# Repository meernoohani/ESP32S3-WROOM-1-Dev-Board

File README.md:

# ESP32-S3-N16R8 Custom Dev Board

A compact, high-performance development board powered by the **ESP32-S3-WROOM-1-N16R8** module, designed in **KiCad 9.0**. This design focuses on maximizing I/O accessibility and providing dual USB-C functionality for both debugging and native USB applications.

## 🛠 Features
* **MCU:** ESP32-S3 (Dual-core @ 240MHz)
* **Memory:** 16MB Flash / 8MB Octal PSRAM (N16R8 variant)
* **Connectivity:**
    * **USB-C (UART):** Dedicated interface for programming and debugging.
    * **USB-C (Native):** Direct access to S3 USB OTG pins.
* **I/O:** Full breakout of all usable GPIOs to 0.1" (2.54mm) headers.
* **Design Tool:** KiCad 9.0

## ⚙️ Hardware Setup
To utilize the 16MB Flash and 8MB PSRAM in your IDE (Arduino/ESP-IDF), use the following settings:

| Setting | Value |
| :--- | :--- |
| **Board** | ESP32S3 Dev Module |
| **Flash Mode** | QIO |
| **Flash Size** | 16MB |
| **PSRAM** | OPI PSRAM |

## 📦 Production Files
This repository includes production-ready files optimized for manufacturing via **JLCPCB**, located in the `/JLCPCB BOM & Gerber Files` folder. This includes:
* Gerber Files
* Drill Files
* BOM (Bill of Materials)
* CPL (Component Placement List / Pick-and-Place)

---
*Note: This project is shared for reference and educational purposes.*

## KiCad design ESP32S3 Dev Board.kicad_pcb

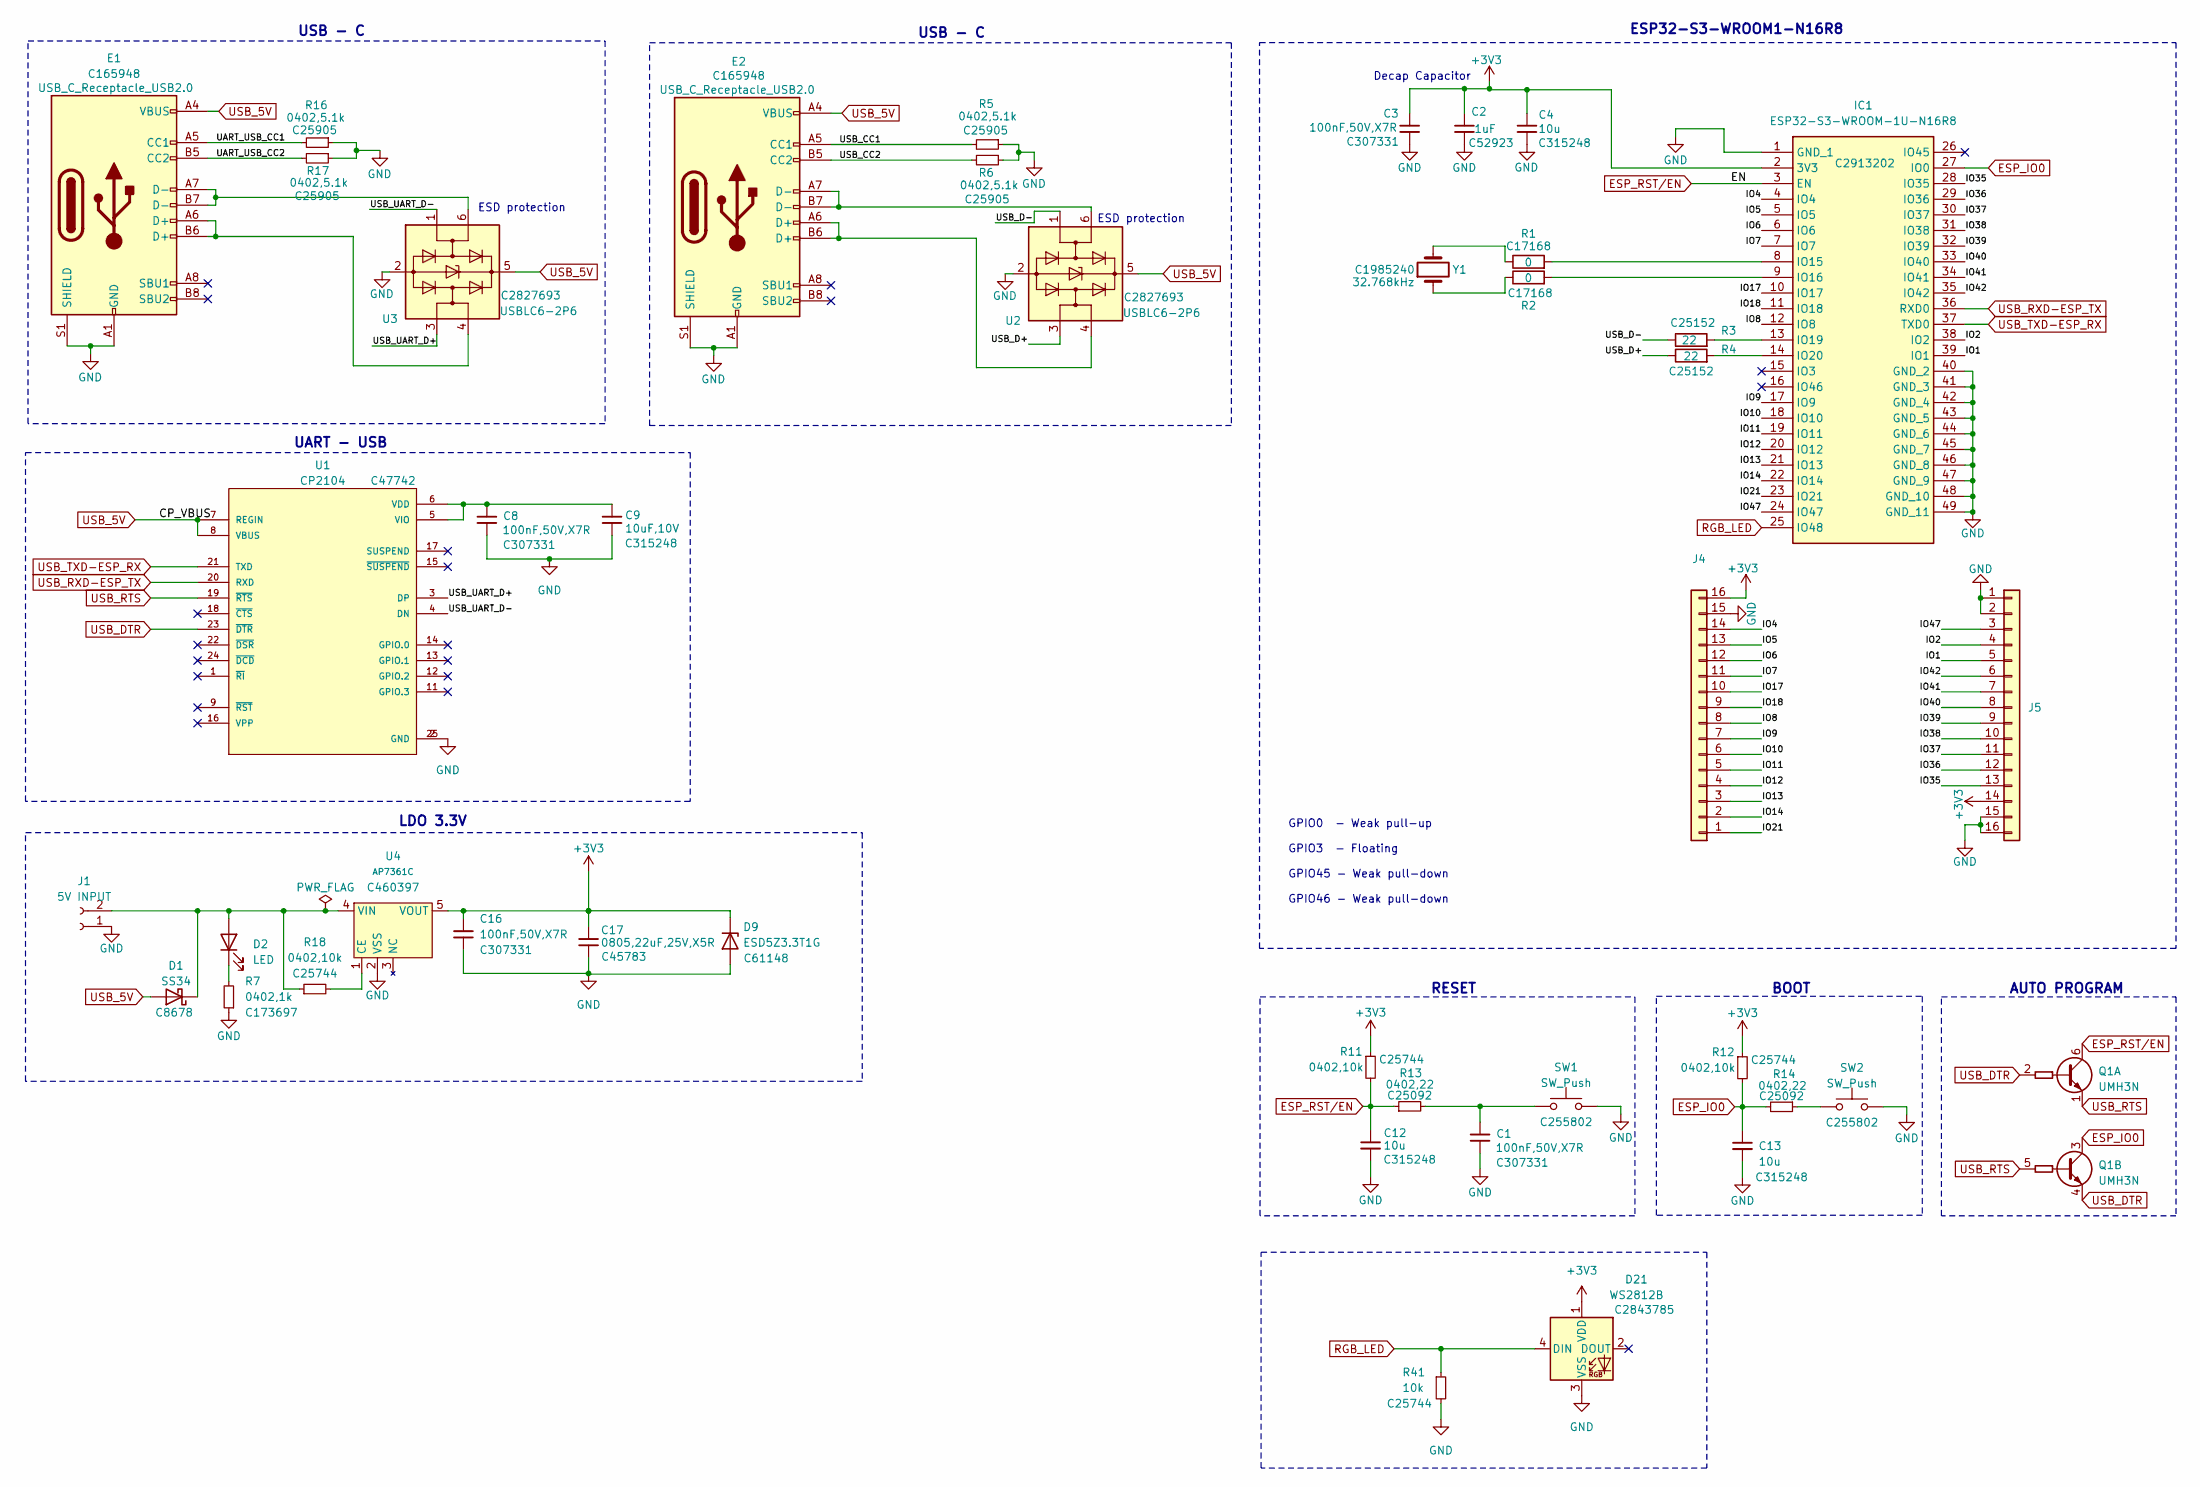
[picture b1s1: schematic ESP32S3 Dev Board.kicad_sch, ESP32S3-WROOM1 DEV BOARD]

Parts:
C1, C3, C8, C16: 100nF,50V,X7R; C_0402_1005Metric; MFGPN CL05B104KB54PNC; LCSC C307331
C2: 1uF; C_0402_1005Metric; MFGPN CL05A105KA5NQNC; LCSC C52923
C4: 10u; C_0402_1005Metric; MFGPN CL05B104KB54PNC; LCSC C315248
C9: 10uF,10V; C_0402_1005Metric; MFGPN CL05B104KB54PNC; LCSC C315248
C12, C13: 10u; C_0402_1005Metric; LCSC C315248
C17: 0805,22uF,25V,X5R; C_0805_2012Metric; MFGPN CL21A226MAQNNNE; LCSC C45783
D1: SS34; D_SMA; LCSC C8678
D2: LED; LED_0603_1608Metric
D9: ESD5Z3.3T1G; D_SOD-523; LCSC C61148
D21: WS2812B; LED_WS2812B_PLCC4_5.0x5.0mm_P3.2mm; LCSC C2843785
E1, E2: USB_C_Receptacle_USB2.0; USB_C; LCSC C165948
IC1: ESP32-S3-WROOM-1U-N16R8; ESP32S3WROOM1UN16R8; Mouser Part Number 356-ESP32S3WM1UN16R8
J1: 5V INPUT; PinHeader_1x02_P2.54mm_Vertical
J4, J5: Conn_01x16; PinHeader_1x16_P2.54mm_Vertical
Q1: UMH3N; SOT-363_SC-70-6; LCSC C62892
R1, R2: 0; C_0402_1005Metric; LCSC C17168
R3, R4: 22; C_0402_1005Metric; LCSC C25152
R5, R6, R16, R17: 0402,5.1k; R_0402_1005Metric; MFGPN 0402WGF5101TCE; LCSC C25905
R7: 0402,1k; R_0402_1005Metric; MFGPN 0402WGF1002TCE; LCSC C173697
R11, R12, R18: 0402,10k; R_0402_1005Metric; MFGPN 0402WGF1002TCE; LCSC C25744
R13, R14: 0402,22; R_0402_1005Metric; MFGPN 0402WGF220JTCE; LCSC C25092
R41: 10k; R_0402_1005Metric; LCSC C25744
SW1, SW2: SW_Push; SW_SPST_CK_RS282G05A3; LCSC C255802
U1: CP2104; CP2104_QFN50P400X400X80-25N; PARTREV 1.0; LCSC C47742
U2, U3: USBLC6-2P6; SOT-666; LCSC C2827693
U4: AP7361C; SOT-89-5; LCSC C460397
Y1: 32.768kHz; Crystal_SMD_3215-2Pin_3.2x1.5mm; LCSC C1985240

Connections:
+3V3: C2.1, C3.1, C4.1, C16.1, C17.1, D9.1 (K), D21.1 (VDD), IC1.2 (3V3), J4.16, J5.14, R11.1, R12.1, U4.5 (VOUT)
/IO1: IC1.39 (IO1), J5.5
/IO2: IC1.38 (IO2), J5.4
/IO4: IC1.4 (IO4), J4.14
/IO5: IC1.5 (IO5), J4.13
/IO6: IC1.6 (IO6), J4.12
/IO7: IC1.7 (IO7), J4.11
/IO8: IC1.12 (IO8), J4.8
/IO9: IC1.17 (IO9), J4.7
/IO10: IC1.18 (IO10), J4.6
/IO11: IC1.19 (IO11), J4.5
/IO12: IC1.20 (IO12), J4.4
/IO13: IC1.21 (IO13), J4.3
/IO14: IC1.22 (IO14), J4.2
/IO17: IC1.10 (IO17), J4.10
/IO18: IC1.11 (IO18), J4.9
/IO21: IC1.23 (IO21), J4.1
/IO35: IC1.28 (IO35), J5.13
/IO36: IC1.29 (IO36), J5.12
/IO37: IC1.30 (IO37), J5.11
/IO38: IC1.31 (IO38), J5.10
/IO39: IC1.32 (IO39), J5.9
/IO40: IC1.33 (IO40), J5.8
/IO41: IC1.34 (IO41), J5.7
/IO42: IC1.35 (IO42), J5.6
/IO47: IC1.24 (IO47), J5.3
/UART_USB_CC1: E1.A5 (CC1), R16.2
/UART_USB_CC2: E1.B5 (CC2), R17.2
/USB_CC1: E2.A5 (CC1), R5.2
/USB_CC2: E2.B5 (CC2), R6.2
/USB_D+: R4.1, U2.3 (I/O2)
/USB_D-: R3.1, U2.1 (I/O1)
/USB_UART_D+: U1.3 (DP), U3.3 (I/O2)
/USB_UART_D-: U1.4 (DN), U3.1 (I/O1)
ESP_IO0: C13.1, IC1.27 (IO0), Q1.3 (C2), R12.2, R14.2
ESP_RST/EN: C12.1, IC1.3 (EN), Q1.6 (C1), R11.2, R13.1
GND: C1.2, C2.2, C3.2, C4.2, C8.2, C9.2, C12.2, C13.2, C16.2, C17.2, D9.2 (A), D21.3 (VSS), E1.A1 (GND), E1.A12 (GND), E1.B1 (GND), E1.B12 (GND), E1.S1 (SHIELD), E2.A1 (GND), E2.A12 (GND), E2.B1 (GND), E2.B12 (GND), E2.S1 (SHIELD), IC1.1 (GND_1), IC1.40 (GND_2), IC1.41 (GND_3), IC1.42 (GND_4), IC1.43 (GND_5), IC1.44 (GND_6), IC1.45 (GND_7), IC1.46 (GND_8), IC1.47 (GND_9), IC1.48 (GND_10), IC1.49 (GND_11), J1.1, J4.15, J5.1, J5.2, J5.15, J5.16, R5.1, R6.1, R7.1, R16.1, R17.1, R41.2, SW1.2, SW2.2, U1.2 (GND), U1.25 (GND), U2.2 (GND), U3.2 (GND), U4.2 (VSS)
unnamed: C1.1, R13.2, SW1.1
unnamed: D1.1 (K), D2.2 (A), J1.2, R18.1, U4.4 (VIN)
unnamed: D2.1 (K), R7.2
unnamed: E1.A6 (D+), E1.B6 (D+), U3.4 (I/O2)
unnamed: E1.A7 (D-), E1.B7 (D-), U3.6 (I/O1)
unnamed: E2.A6 (D+), E2.B6 (D+), U2.4 (I/O2)
unnamed: E2.A7 (D-), E2.B7 (D-), U2.6 (I/O1)
unnamed: IC1.8 (IO15), R1.2
unnamed: IC1.9 (IO16), R2.2
unnamed: IC1.13 (IO19), R3.2
unnamed: IC1.14 (IO20), R4.2
unnamed: R1.1, Y1.2
unnamed: R2.1, Y1.1
unnamed: R14.1, SW2.1
unnamed: C8.1, C9.1, U1.5 (VIO), U1.6 (VDD)
unnamed: R18.2, U4.1 (CE)
RGB_LED: D21.4 (DIN), IC1.25 (IO48), R41.1
USB_5V: D1.2 (A), E1.A4 (VBUS), E1.A9 (VBUS), E1.B4 (VBUS), E1.B9 (VBUS), E2.A4 (VBUS), E2.A9 (VBUS), E2.B4 (VBUS), E2.B9 (VBUS), U1.7 (REGIN), U1.8 (VBUS), U2.5 (VBUS), U3.5 (VBUS)
USB_DTR: Q1.2 (B1), Q1.4 (E2), U1.23 (~DTR)
USB_RTS: Q1.1 (E1), Q1.5 (B2), U1.19 (~RTS)
USB_RXD-ESP_TX: IC1.36 (RXD0), U1.20 (RXD)
USB_TXD-ESP_RX: IC1.37 (TXD0), U1.21 (TXD)

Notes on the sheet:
BOOT
GPIO0 - Weak pull-up GPIO3 - Floating GPIO45 - Weak pull-down GPIO46 - Weak pull-down
Decap Capacitor
LDO 3.3V
USB - C
ESD protection
RESET
UART - USB
ESP32-S3-WROOM1-N16R8
AUTO PROGRAM

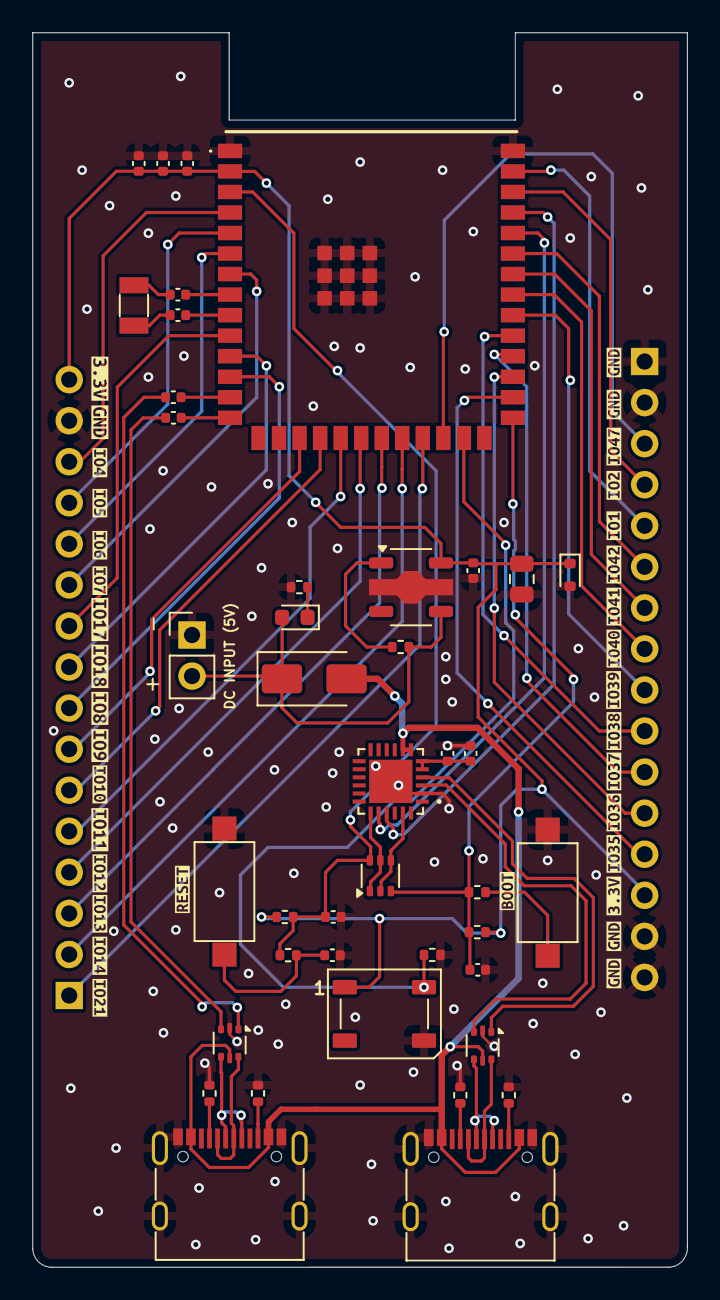
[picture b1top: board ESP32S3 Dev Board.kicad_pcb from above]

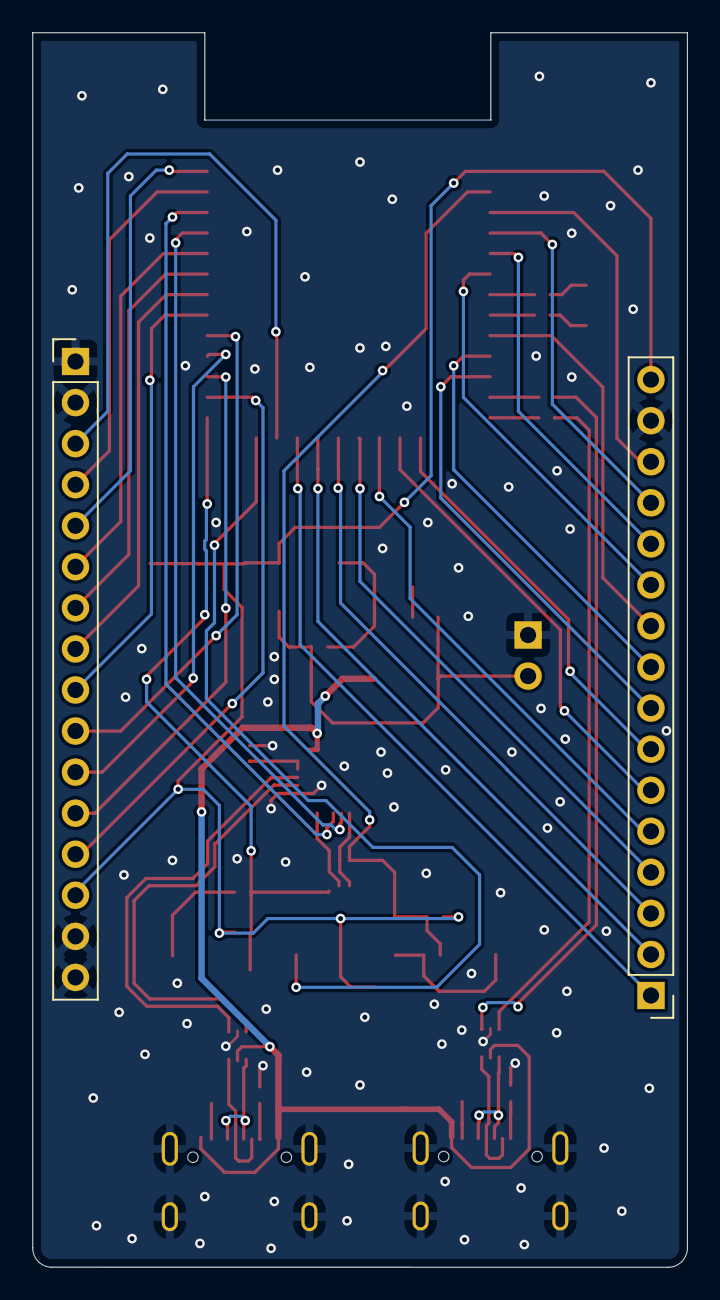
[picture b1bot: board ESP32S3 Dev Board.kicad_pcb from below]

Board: 2 copper layers, 40.5 x 76.4 mm, 77 parts (2 on the bottom side), 59 nets.

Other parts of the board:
kibuzzard-6988DF0D: G***; kibuzzard-6988DF0D
kibuzzard-6988DF05: G***; kibuzzard-6988DF05
kibuzzard-6988DF41: G***; kibuzzard-6988DF41
kibuzzard-6988DF49: G***; kibuzzard-6988DF49
kibuzzard-6988DF59: G***; kibuzzard-6988DF59
kibuzzard-6988DF68: G***; kibuzzard-6988DF68
kibuzzard-6988DF80: G***; kibuzzard-6988DF80
kibuzzard-6988E0B4: G***; kibuzzard-6988E0B4
kibuzzard-6988E0BB: G***; kibuzzard-6988E0BB
kibuzzard-6988E02D: G***; kibuzzard-6988E02D
kibuzzard-6988E04D: G***; kibuzzard-6988E04D
kibuzzard-6988E09C: G***; kibuzzard-6988E09C
kibuzzard-6988E10C: G***; kibuzzard-6988E10C
kibuzzard-6988E12C: G***; kibuzzard-6988E12C
kibuzzard-6988E13F: G***; kibuzzard-6988E13F
kibuzzard-6988E14E: G***; kibuzzard-6988E14E
kibuzzard-6988E15C: G***; kibuzzard-6988E15C
kibuzzard-6988E16F: G***; kibuzzard-6988E16F
kibuzzard-6988E025: G***; kibuzzard-6988E025
kibuzzard-6988E039: G***; kibuzzard-6988E039
kibuzzard-6988E063: G***; kibuzzard-6988E063
kibuzzard-6988E091: G***; kibuzzard-6988E091
kibuzzard-6988E101: G***; kibuzzard-6988E101
kibuzzard-6988E107: G***; kibuzzard-6988E107
kibuzzard-6988E119: G***; kibuzzard-6988E119
kibuzzard-6988E120: G***; kibuzzard-6988E120
kibuzzard-6988E134: G***; kibuzzard-6988E134
kibuzzard-6988E146: G***; kibuzzard-6988E146
kibuzzard-6988E155: G***; kibuzzard-6988E155
kibuzzard-6988E162: G***; kibuzzard-6988E162
kibuzzard-6988E169: G***; kibuzzard-6988E169
kibuzzard-6988E176: G***; kibuzzard-6988E176
kibuzzard-6988EF1E: G***; kibuzzard-6988EF1E
kibuzzard-6988EF30: G***; kibuzzard-6988EF30

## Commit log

2026-02-08 init
2026-02-08 Add README for ESP32-S3-N16R8 custom dev board
    Added detailed information about the ESP32-S3-N16R8 custom dev board, including features, hardware setup, and production files.
2026-02-21 License
